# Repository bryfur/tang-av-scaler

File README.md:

# tang-av-scaler

An FPGA video scaler for the sixth generation of game consoles (PlayStation 2, Xbox, GameCube):
480i component video and stereo sound in, 1080p60 HDMI out, about 2 ms behind the console. A Sipeed
Tang Mega 138K SOM (Gowin GW5AST-138) on a carrier board of its own, with a Seeed XIAO ESP32-C5 for
Wi-Fi. The board, the FPGA design, the software for the FPGA's CPU and the ESP32's firmware are all
here.

```
console: component video (YPbPr, 480i) + stereo audio
  -> ADV7181D decoder, PCM1808 audio converter
  -> GW5AST-138 FPGA
       fields into DDR3 -> motion adaptive deinterlace + noise reduction -> SMAA
       -> FSR 1 upscale (EASU) -> FSR 1 sharpen (RCAS) -> on-screen text -> HDMI coding
       its hard RISC-V CPU: bring-up, settings, frame lock, on-screen text
  -> the FPGA's transceivers -> SN65DP159 -> HDMI 1080p60 with sound
  XIAO ESP32-C5: Wi-Fi, web page, updates, JTAG; talks to the CPU over SPI
```

Status (2026-11-12): the board (rev C-B) is built and runs a console's picture and sound to a
display and a capture device. The table below is what it does now, on the board. The console it
has been run with is a PlayStation 2; an Xbox or a GameCube with its component cable puts out the
same signal (480i, YPbPr, 59.94 Hz) and has not been tried yet.

The board, rev C-B ([hardware/av-board/](hardware/av-board/README.md)), as designed (rendered, and from above) and as built:
the SOM under its heat sink, the XIAO and its antenna at the right; along the back edge the HDMI
output, the two audio jacks, power (USB-C) and the three component video jacks.

A frame as it leaves for the display, the on-screen display on (read back from the FPGA: no camera,
no capture device).

Tales of the Abyss, one frozen frame, shown two ways in turn (two seconds each): the console's 480i
stretched the plain way, then the scaler's output; the corner says which.
[Drag a line between them yourself](https://bryfur.github.io/tang-av-scaler/compare/?frame=abyss).

## What it does

| | |
|---|---|
| Input | 480i component (YPbPr) through an ADV7181D, sampled line-locked at 13.5 MHz; stereo analogue audio through a PCM1808. The decoder's sampling phase can be set, or tuned to the console's pixels (every phase tried on a still picture, the sharpest kept). |
| Deinterlacing | Motion adaptive from the last four fields, kept in the SOM's DDR3: a field's lines as they are, the lines between from the field before where nothing moves and from their neighbours where something does. Bob and weave can be chosen instead. |
| Noise | Where the picture is still, each sample is averaged with the same one a frame earlier (off, or three strengths). |
| Anti-aliasing | SMAA 1x on the 480-line picture: luma edges, the orthogonal and the diagonal patterns, corners kept. A view that paints what it finds (edges, blends) in the picture's place, for tuning. |
| Scaling | FSR 1's edge adaptive upsampling (EASU) to 1440 x 1080 (4:3) or 1920 x 1080 (16:9, for a game's widescreen mode). Any part of the source can be shown: the black border round a game's picture is measured and left out, so the picture fills the screen (or the part is set by hand). |
| Sharpening | FSR 1's RCAS on luma, in 16 steps, with its noise term (less where a pixel is noise rather than detail). |
| Timing | The output's frames are kept in step with the input's fields (the CPU trims the clock generator: within 10 us, no field shown twice or left out). A frame is made from the field that is still coming in: about 2 ms from a line captured to it sent (16.8 ms with whole fields). |
| Output | 1080p60 (59.94 Hz) HDMI from the FPGA's own transceivers; the console's sound as HDMI audio (two channels of L-PCM at 48 kHz, its clock from the PLL the pixel clock comes from); AVI and audio InfoFrames. Runs a display, a capture device and an AV receiver (picture and sound). |
| On screen | An on-screen display: what comes in and goes out, what is done to the picture, the delay, the lock, the FPGA's temperature. |
| Control | A web page on the XIAO: every setting (applied as it is changed, kept across power cycles), status, a screen capture of the output read back from the FPGA, firmware update over Wi-Fi. |

## What it looks like

Two frozen frames, each in and out: Killzone (PS2, its widescreen mode) and Tales of the Abyss
(PS2, 4:3). "The plain way" is the
two 480i fields as the console sent them, woven into a frame and stretched to 1080p (bilinear),
which is about what a simple scaler or a display does. "The scaler" is its 1080p output (motion
adaptive deinterlacing, noise reduction medium, SMAA with diagonals and corners at edge threshold
12, FSR 1 with sharpening 8/16). Nothing went through a camera or a capture device: the fields are
read out of the FPGA's memory and the output is read back from its last stage, pixel for pixel
(`gateware/tools/still.py`).

**[Drag to compare](https://bryfur.github.io/tang-av-scaler/compare/)**: both frames on a page with a
line to drag between the plain picture and the scaler's, at any size up to four screen pixels a
pixel (`docs/compare/index.html`).

The pictures themselves, in [`docs/compare/`](docs/compare/):

- Whole frames, 1920 x 1080. Killzone: [the plain way](docs/compare/game-plain.png),
  [the scaler](docs/compare/game-scaler.png), [a half of each](docs/compare/game-split.png).
  Tales of the Abyss: [the plain way](docs/compare/abyss-plain.png),
  [the scaler](docs/compare/abyss-scaler.png), [a half of each](docs/compare/abyss-split.png).
- The frames as they came, the fields woven and nothing else (720 x 480):
  [Killzone](docs/compare/game-480i.png), [Tales of the Abyss](docs/compare/abyss-480i.png).
- Parts of Killzone side by side, three times the size: [the tower and its guy wires](docs/compare/tower.png),
  [palms](docs/compare/palms.png), [hanging foliage](docs/compare/foliage.png),
  [HUD text](docs/compare/hud-text.png), [the ammunition counter](docs/compare/ammo.png).

## How it is put together

- **The picture's path is logic** (`gateware/rtl/`): every pixel, at 148.5 MHz out. Each block has a
  model in Python (`gateware/sim/`) and the whole path is simulated against them pixel for pixel:
  the deinterlacer, SMAA, the scaler and the sharpening give exactly the models' pictures.
- **Everything else runs on the FPGA's hard CPU** (an Andes A25 RISC-V in the GW5AST, `gateware/sw/`,
  no operating system): it brings the board's chips up, holds the settings, finds the picture's
  border, tunes the sampling phase, keeps the output in step with the input, writes the on-screen
  text. A new program is loaded in a second, with no new bitstream.
- **The XIAO ESP32-C5** (`firmware/xiao-wifi/`) is the way in: Wi-Fi, the web page, updates, and
  JTAG to load bitstreams. It talks to the CPU over SPI in small messages, keeps the settings for
  when the power is off, and carries the CPU's program.

The design uses 16 % of the FPGA's logic, 75 % of its block RAM and 15 % of its multipliers.

## Measured on the board

| | |
|---|---|
| Delay | 2.0 ms at the top of the picture (some 2.5 ms at the bottom, by the two scan rates) with the picture made from the field coming in; 16.8 ms with whole fields. From the FPGA's own timing of a frame's start against the field; not yet measured from outside, and a display adds its own. |
| Frame lock | within 10 us of its mark, the clock trimmed by some -57 ppm (this console against this board); in step some 20 s after starting 5 ms off |
| Noise | the spread in a frozen frame's flat areas: 2.32 as it comes, 1.98 with the noise reduction; sharpened fully 3.94, with the sharpening's noise term 3.12, with both 2.61 |
| Sampling phase | 4.5 % between the sharpest and the least sharp phase on Killzone (its picture is soft to begin with) |
| Screen capture | 480 x 270 in 2 s, 960 x 540 in 6 s over the web page |

## What is not done

- Consoles other than the PlayStation 2 have not been tried. The Xbox and the GameCube put out the
  same 480i over their component cables; the Dreamcast has no component output (its VGA and RGB
  would come in at the board's inputs that are not used yet).
- Inputs other than 480i: 480p, 576i, 720p and 1080i need the decoder's settings and the capture's
  timing for each.
- 4K output: a 2160p30 test picture is clean on a display; at 2160p60 the link runs and the display
  sees scrambling but shows nothing; the scaler's own path ends at 1080p.
- The board's other inputs (S/PDIF, VGA, RGB with SCART sync) are wired but not used.
- Without the XIAO the CPU starts with its built-in settings: it has no storage of its own.
- At power-on the FPGA loads its image twice, some 20 s more before there is a picture: configured
  before the clock generator runs, one transceiver lane's clock comes up wrong and the lanes'
  resets do not clear it; the XIAO sees that and has the FPGA load again. The right reset is not
  found yet.
- A bitstream into the FPGA's SRAM over Wi-Fi (`avx.py load`) goes in, and the XIAO then restarts
  with the FPGA left unloaded; over USB it works (`gateware/tools/load.sh`).
- The delay has not been measured through a display with a camera or a light sensor.

## The repository

| Directory | What |
|---|---|
| [`hardware/av-board/`](hardware/av-board/README.md) | The board, rev C-B: generated with KiCad's Python API from `rev-cb/board.py`, every circuit from its part's reference design and reviewed against the data sheets; fab files for JLCPCB. Earlier designs that were not built are in `older/`. |
| [`gateware/`](gateware/README.md) | The FPGA design: `rtl/` the logic, `sw/` the CPU's program, `sim/` the models and testbenches, `gowin/` the build, `tools/` the host's scripts (registers, loading, stills), `docs/` notes. |
| [`firmware/xiao-wifi/`](firmware/xiao-wifi/README.md) | The XIAO ESP32-C5's firmware: Wi-Fi, the web page, updates, a JTAG server, the link to the FPGA's CPU. (`firmware/xiao/` is an earlier USB-only bridge for an ESP32-S3.) |

Building and loading: [gateware/README.md](gateware/README.md) (the bitstream and the CPU's
program: Gowin's tools, a RISC-V GCC) and [firmware/xiao-wifi/README.md](firmware/xiao-wifi/README.md)
(ESP-IDF). With the bitstream in the SOM's flash and the firmware in the XIAO, the board needs
power, a console and a display.

## Reference documents

`hardware/av-board/refs/` (not in git: the vendors' copyright) holds the data sheets and user
guides the circuits follow; [hardware/av-board/README.md](hardware/av-board/README.md) lists which
and where each came from. The scaler's algorithms: SMAA (Jimenez et al.) and AMD's FidelityFX Super
Resolution 1 (EASU and RCAS, MIT licence), both written again for this hardware
(`gateware/sim/smaa.py`, `gateware/sim/fsr.py` say how they differ).

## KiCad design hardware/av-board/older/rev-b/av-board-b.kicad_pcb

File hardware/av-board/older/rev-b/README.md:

# AV board rev B

Rev A with the ADV7842 (256-ball BGA) replaced by the ADV7181D (64-lead LFCSP): component video
into the ADV7181D, stereo audio into a PCM1808, HDMI out of an ADV7511. Four layers, no BGA.

Status: reviewed against every part's data sheet (review.md), routed, DRC clean, fab files made;
not ordered.

- [design.md](design.md): what changed from rev A, and the ADV7181D's circuit with its sources
- [review.md](review.md): every part checked against its data sheet, with the fixes
- `board.py`, `gen_pcb.py`: the sources; made as in [../README.md](../../README.md)

## Ordering at JLCPCB

`fab/av-board-b-gerbers.zip` for the board; for assembly, one of:

| BOM + CPL | Assembled by JLCPCB | By hand |
|---|---|---|
| `fab/av-board-b-bom.csv`, `fab/av-board-b-cpl.csv` | everything (230 parts) | nothing |
| `fab/av-board-b-hand-jacks-bom.csv`, `fab/av-board-b-hand-jacks-cpl.csv` | everything but the RCA jacks (225 parts) | J1-J5: CUI RCJ-014 (yellow) for Y, Pb and L, RCJ-012 (red) for Pr and R, LCSC C4991844 / C4991691, or any RCJ-01x |

Settings the files do not carry:

- 4 layers, 1.6 mm, stack-up **JLC04161H-7628**: F.Cu signal / In1 GND / In2 GND / B.Cu signal
  (the TMDS geometry assumes the 0.21 mm 7628 prepreg under each outer layer). Impedance control
  on: the TMDS pairs are 0.25 mm lines with a 0.25 mm gap on F.Cu, 103 R differential by
  IPC-2141. Confirm in JLCPCB's impedance calculator (outer layer, W 0.25, S 0.25). The voids
  in In1 and In2 under the ESD arrays' TMDS pads are meant (TI SPRAAR7 3.14; review.md's TMDS
  layout row, `kit/hdmi_audit.py rev-b`).
- Vias 0.5/0.3 mm, and four 0.4/0.2 mm ones at the ESD arrays' GND pads (inside JLCPCB's
  0.3/0.15 mm four-layer minimum; check the quote does not add a small-via charge). Minimum track
  and space 0.127 mm.
- Assembly: **top side only**: every SMT part is on the top. Underneath are only the J9/J10
  sockets (through-hole, soldered from the top). Through-hole parts: the two sockets, HDMI's
  shell, and the RCA jacks unless they are left for hand soldering.
- The XIAO itself is not on the BOM: any Seeed XIAO (ESP32-C3, -S3 or -C6) plugs into J11/J12,
  its USB-C towards the HDMI side (silkscreen "XIAO, USB >"). J7 (SCART sync) is a plain 2-pin
  header: SYNC, GND. J13 (S/PDIF) is a 5-pin header: COAX, GND, OPT, GND, 5V (design.md). J8 (VGA) is a 2 x 8 header,
  pin n the DE-15's pin n, for a bracket cable.
- Check every part's rotation in JLCPCB's placement preview, mainly U1 (the ADV7181D: pin 1 at
  the dot, AIN10 at its top left), U2, U3, the regulators and the three resistor arrays RN1-RN3,
  and the RCA jacks' barrels over the edge (the CPL turns the yellow ones 90 degrees for JLCPCB's
  footprint, kit/gen_fab.py JLC_TURN; the red RCJ-012 has no model there and is placed as drawn,
  as the black RCJ-011).

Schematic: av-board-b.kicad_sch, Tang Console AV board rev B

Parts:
C1, C2: 22u; C_0805_2012Metric; LCSC C45783
C3, C5, C6, C7, C8, C25, C26, C27, C32, C33, C35, C38, C41, C43, C46, C47, C48, C49, C50, C52, C54, C56, C58, C60, C63, C65, C67, C73, C74, C75, C76, C77, C81, C82, C83, C84, C85, C86, C87, C88, C89, C90, C91, C92: 100n; C_0402_1005Metric; LCSC C1525
C4, C9, C11, C12, C14, C15, C17, C18, C20: 10u; C_0805_2012Metric; LCSC C15850
C10: 6.8p; C_0402_1005Metric; LCSC C1576
C13, C16, C19, C69, C71: 220p; C_0402_1005Metric; LCSC C1530
C21, C22, C23, C24, C64, C66, C68, C78, C79, C80: 10u; C_0603_1608Metric; LCSC C19702
C28, C29: 1n; C_0402_1005Metric; LCSC C1523
C30, C31: 33p; C_0402_1005Metric; LCSC C1562
C34, C37, C40, C42: 10u; C_0402_1005Metric; LCSC C15525
C36, C39, C45, C51, C53, C55, C57, C59, C61: 10n; C_0402_1005Metric; LCSC C15195
C44: 82n; C_0402_1005Metric; LCSC C277511
C62, C70, C72: 1u; C_0603_1608Metric; LCSC C15849
D1, D3: B5819W; D_SOD-123; LCSC C8598
D2: KT-0603R; LED-SMD_L1.6-W0.8-R-RD; LCSC C2286
D7: 1N4148WS; D_SOD-323; LCSC C2128
D8, D9, D10, D11, D12, D13: TPD1E05U06DPYR; X1SON-2_L1.0-W0.6-P0.65-RD-1; LCSC C436349
F1, F2: 0.2A; F0805; LCSC C883105
FB1, FB2, FB3, FB4: 120R; L_0603_1608Metric; LCSC C14709
J1: RCA Y; CONN-TH_RCJ-011; LCSC C4991844
J2: RCA Pb; CONN-TH_RCJ-011; LCSC C4991844
J3: RCA Pr; CONN-TH_RCJ-011; LCSC C4991691
J4: RCA L; CONN-TH_RCJ-011; LCSC C4991844
J5: RCA R; CONN-TH_RCJ-011; LCSC C4991691
J6: HDMI-001; HDMI-SMD_19P-P0.50-H-F; LCSC C138388
J7: SYNC; HDR-TH_2P-P2.54-V-M; LCSC C492401
J8: VGA; HDR-TH_16P-P2.54-V-M-R2-C8-S2.54; LCSC C68234
J9, J10: 2x20 socket; HDR-TH_40P-P2.54-V-F-R2-C20-S2.54-2; LCSC C5124634
J11: XIAO 5V..D7; HDR-TH_7P-P2.54-V-F; LCSC C22438157
J12: XIAO D0..D6; HDR-TH_7P-P2.54-V-F; LCSC C22438157
J13: SPDIF; HDR-TH_5P-P2.54-V-M; LCSC C492404
L1: 2.2uH; IND-SMD_L3.0-W3.0_FNR30XXS; LCSC C167747
L2, L3, L4: 10uH; IND-SMD_L4.0-W4.0_SMNR4012; LCSC C222882
Q1, Q2: 2N7002; SOT-23-3_L2.9-W1.3-P1.90-LS2.4-BR; LCSC C8545
R1, R2, R7, R8, R9, R10, R11, R12, R41, R45, R46, R53, R54, R55, R57, R59, R77: 10k; R_0402_1005Metric; LCSC C25744
R3, R5, R6: 470; R_0402_1005Metric; LCSC C25117
R4, R14, R63: 100k; R_0402_1005Metric; LCSC C25741
R13: 499k; R_0402_1005Metric; LCSC C25793
R15: 169k; R_0402_1005Metric; LCSC C25758
R16, R18, R20: 30.1k; R_0402_1005Metric; LCSC C29402
R17, R19: 78.7k; R_0402_1005Metric; LCSC C67239
R21, R22, R23, R24, R42, R43, R44, R60: 75; R_0603_1608Metric; LCSC C4275
R25, R61: 1M; R_0402_1005Metric; LCSC C26083
R26: 1.69k; R_0402_1005Metric; LCSC C25870
R27, R28, R29, R30, R31, R32, R33, R34, R47, R48, R62, R64: 33; R_0402_1005Metric; LCSC C25105
R35, R36, R37, R38, R39, R40, R49, R51: 4.7k; R_0402_1005Metric; LCSC C25900
R50, R52: 47k; R_0402_1005Metric; LCSC C25792
R56, R58: 12k; R_0402_1005Metric; LCSC C25752
R65, R66, R67, R68, R69: 49.9; R_0402_1005Metric; LCSC C25120
R70: 887; R_0402_1005Metric; LCSC C55968414
R71, R72, R73, R74, R75, R76: 2k; R_0402_1005Metric; LCSC C4109
R78: 27k; R_0402_1005Metric; LCSC C25771
RN1, RN2, RN3: 33; RES-ARRAY-SMD_0402-8P-L2.0-W1.0-BL; LCSC C25501
SW1, SW2: TS-1187A-B-A-B; SW-SMD_4P-L5.1-W5.1-P3.70-LS6.5-TL_H1.5; LCSC C318884
U1: ADV7181DBCPZ-RL; LFCSP-64_L9.0-W9.0-P0.50-BL-EP7.1; LCSC C514378
U2: ADV7511KSTZ; LQFP-100_L14.0-W14.0-P0.50-LS16.0-BL; LCSC C179459
U3: PCM1808PWR; TSSOP-14_L5.0-W4.4-P0.65-LS6.4-BL; LCSC C55513
U4: TLV62569DBVR; SOT-23-5_L3.0-W1.7-P0.95-LS2.8-BR; LCSC C141836
U5, U6, U7: TPS7A7001DDAR; SOIC-8_L4.9-W3.9-P1.27-LS6.0-BL-EP; LCSC C60719
U8, U9, U10, U19, U20: TPD4E05U06DQAR; USON-10_L2.5-W1.0-P0.50-BL; LCSC C138714
U12: TPS7A2045PDBVR; SOT-23-5_L2.9-W1.6-P0.95-LS2.8-BR; LCSC C2873627
U13: SN74LVC1GU04DBVR; SOT-23-5_L3.0-W1.7-P0.95-LS2.8-BR; LCSC C81934
U14, U15: SN74LVC1G04DBVR; SOT-23-5_L3.0-W1.7-P0.95-LS2.8-BR; LCSC C7827
U21: SN74LVC2G17DBVR; SOT-23-6_L2.9-W1.6-P0.95-LS2.8-BL; LCSC C10429
U22: SN74LVC8T245PWR; TSSOP-24_L7.8-W4.4-P0.65-LS6.4-BL; LCSC C27643
U23: SN74AVC4T245PWR; TSSOP-16_L5.0-W4.4-P0.65-LS6.4-BL; LCSC C81461
Y1: 28.63636MHz 20pF; CRYSTAL-SMD_L5.0-W3.2; LCSC C112564

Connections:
1V8A: C16.1, C17.1, D1.2 (A), FB1.1, FB2.1, R17.1, U6.6 (OUT)
1V8B: C19.1, C20.1, L2.1, L3.1, L4.1, R19.1, U7.6 (OUT)
3V3: C6.1, C8.1, C13.1, C14.1, C15.1, C18.1, C49.1, C67.1, C68.1, C75.1, C76.1, C77.1, C91.1, D1.1 (K), FB3.1, FB4.1, Q1.1 (G), Q2.1 (G), R1.1, R2.1, R10.2, R11.2, R12.2, R15.1, R35.1, R36.1, R49.1, R51.1, R71.1, R72.1, R73.1, R78.1, U2.47 (MVDD), U3.4 (VDD), U5.6 (OUT), U6.2 (EN), U6.3 (IN), U7.2 (EN), U7.3 (IN), U13.5 (VCC), U14.5 (VCC), U15.5 (VCC), U21.5 (VCC), U22.23 (VCCB), U22.24 (VCCB), U23.16 (VCCB)
3V6: C10.1, C11.1, C12.1, L1.2, R13.1, U5.2 (EN), U5.3 (IN)
5VA: C65.1, C66.1, U3.3 (VCC), U12.5 (OUT)
+5V: C1.1, C2.1, C3.1, C9.1, C62.1, D3.2 (A), F1.1, F2.1, J9.11, J10.11, U4.1 (EN), U4.4 (VIN), U12.1 (IN), U12.3 (EN)
AIN_PB: C26.2, U1.47 (AIN8)
AIN_PR: C27.2, U1.45 (AIN6)
AIN_VB: C48.2, U1.48 (AIN9)
AIN_VG: C47.2, U1.35 (AIN2)
AIN_VR: C46.2, U1.46 (AIN7)
AIN_Y: C25.2, U1.49 (AIN10)
ALSB: R39.2, U1.52 (ALSB)
AUD_DIV_L: C69.1, C70.1, R56.2, R57.1
AUD_DIV_R: C71.1, C72.1, R58.2, R59.1
AUD_VINL: C70.2, U3.13 (VINL)
AUD_VINR: C72.2, U3.14 (VINR)
AV_AVDD: C23.1, C60.1, C61.1, FB3.2, U1.41 (AVDD)
AV_C0: R31.1, U1.26 (P2)
AV_C1: R30.1, U1.25 (P3)
AV_C2: RN3.3, U1.19 (P4)
AV_C3: RN3.2, U1.18 (P5)
AV_C4: RN3.1, U1.17 (P6)
AV_C5: R29.1, U1.16 (P7)
AV_C6: R28.1, U1.15 (P8)
AV_C7: R27.1, U1.14 (P9)
AV_DE: R34.1, U1.63 (FIELD/DE)
AV_DVDD: C21.1, C54.1, C55.1, C56.1, C57.1, FB1.2, U1.23 (DVDD), U1.58 (DVDD)
AV_DVDDIO: C24.1, C50.1, C51.1, C52.1, C53.1, FB4.2, R38.1, R39.1, R40.1, U1.4 (DVDDIO), U1.11 (DVDDIO)
AV_HS: R32.1, U1.2 (HS/CS)
AV_LLC: RN3.4, U1.20 (LLC)
AV_PVDD: C22.1, C44.2, C45.2, C58.1, C59.1, FB2.2, U1.31 (PVDD)
AV_VS: R33.1, U1.64 (VS)
AV_Y0: RN2.4, U1.8 (P12)
AV_Y1: RN2.3, U1.7 (P13)
AV_Y2: RN2.2, U1.6 (P14)
AV_Y3: RN2.1, U1.5 (P15)
AV_Y4: RN1.4, U1.62 (P16)
AV_Y5: RN1.3, U1.61 (P17)
AV_Y6: RN1.2, U1.60 (P18)
AV_Y7: RN1.1, U1.59 (P19)
CAPC2: C37.1, C38.1, C39.1, U1.44 (CAPC2)
CAPY1: C34.1, C35.1, C36.1, U1.39 (CAPY1)
CAPY2: C32.1, C33.1, C34.2, C35.2, C36.2, C37.2, C38.2, C39.2, U1.40 (CAPY2)
CEC_PU: D7.2 (A), R78.2
CML: C42.1, C43.1, U1.43 (CML)
ELPF: C45.1, R26.1, U1.30 (ELPF)
ELPF_RC: C44.1, R26.2
ESP_CS: J9.32, R10.1, U22.21 (B1)
ESP_IRQ: J9.33, R11.1, U23.13 (1B1)
ESP_MISO: J9.35, R12.1, U23.12 (1B2)
ESP_MOSI: J9.36, U22.19 (B3)
ESP_SCK: J9.34, U22.20 (B2)
FB_1V8A: C16.2, R17.2, R18.1, U6.7 (FB)
FB_1V8B: C19.2, R19.2, R20.1, U7.7 (FB)
FB_3V3: C13.2, R15.2, R16.1, U5.7 (FB)
FB_3V6: C10.2, R13.2, R14.1, U4.5 (FB)
FMT: R55.1, U3.12 (FMT)
GND: C1.2, C2.2, C3.2, C4.2, C5.2, C6.2, C7.2, C8.2, C9.2, C11.2, C12.2, C14.2, C15.2, C17.2, C18.2, C20.2, C21.2, C22.2, C23.2, C24.2, C30.2, C31.2, C32.2, C33.2, C40.2, C41.2, C42.2, C43.2, C49.2, C50.2, C51.2, C52.2, C53.2, C54.2, C55.2, C56.2, C57.2, C58.2, C59.2, C60.2, C61.2, C62.2, C63.2, C64.2, C65.2, C66.2, C67.2, C68.2, C69.2, C71.2, C73.2, C75.2, C76.2, C77.2, C78.2, C79.2, C80.2, C81.2, C82.2, C83.2, C84.2, C85.2, C86.2, C87.2, C88.2, C89.2, C90.2, C91.2, C92.2, D2.2 (K), D8.2 (GND), D9.2 (GND), D10.2 (GND), D11.2 (GND), D12.2 (GND), D13.2 (GND), J1.1, J2.1, J3.1, J4.1, J5.1, J6.2 (TMDSData2Shield), J6.5 (TMDSData1Shield), J6.8 (TMDSData0Shield), J6.11 (TMDSClockShield), J6.17 (DDC/CECGround), J6.20, J6.21, J6.22, J6.23, J7.2, J8.5, J8.6, J8.7, J8.8, J8.10, J9.12, J10.12, J10.37, J10.38, J10.39, J10.40, J11.2, J13.2, J13.4, R4.2, R9.2, R14.2, R16.2, R18.2, R20.2, R21.2, R22.2, R23.2, R24.2, R37.2, R41.2, R42.2, R43.2, R44.2, R45.2, R46.2, R53.2, R54.2, R55.2, R57.2, R59.2, R60.2, R63.2, R70.2, R74.2, R77.2, SW1.4 (D), SW2.4 (D), U1.3 (GND), U1.10 (GND), U1.24 (GND), U1.57 (GND), U1.65 (EP), U2.3 (DSD0), U2.4 (DSD1), U2.5 (DSD2), U2.6 (DSD3), U2.7 (DSD4), U2.8 (DSD5), U2.9 (DSDCLK), U2.13 (I2S1), U2.14 (I2S2), U2.15 (I2S3), U2.18 (GND), U2.20 (GND), U2.22 (GND), U2.23 (GND), U2.27 (GND), U2.31 (GND), U2.37 (GND), U2.44 (GND), U2.51 (HEAC-), U2.52 (HEAC+), U2.57 (D35), U2.58 (D34), U2.59 (D33), U2.60 (D32), U2.61 (D31), U2.62 (D30), U2.63 (D29), U2.64 (D28), U2.65 (D27), U2.66 (D26), U2.67 (D25), U2.68 (D24), U2.75 (GND), U2.89 (D7), U2.90 (D6), U2.91 (D5), U2.92 (D4), U2.93 (D3), U2.94 (D2), U2.95 (D1), U2.96 (D0), U2.99 (GND), U2.100 (GND), U3.2 (AGND), U3.5 (DGND), U4.2 (GND), U5.1 (NC), U5.4 (NC), U5.5 (NC), U5.8 (GND), U5.9 (EP), U6.1 (NC), U6.4 (NC), U6.5 (NC), U6.8 (GND), U6.9 (EP), U7.1 (NC), U7.4 (NC), U7.5 (NC), U7.8 (GND), U7.9 (EP), U8.3 (GND), U8.8 (GND), U9.3 (GND), U9.8 (GND), U10.3 (GND), U10.8 (GND), U12.2 (GND), U13.3 (GND), U14.3 (GND), U15.3 (GND), U19.3 (GND), U19.8 (GND), U20.3 (GND), U20.8 (GND), U21.2 (GND), U22.6 (A4), U22.7 (A5), U22.8 (A6), U22.9 (A7), U22.10 (A8), U22.11 (GND), U22.12 (GND), U22.13 (GND), U22.22 (~OE), U23.2 (1DIR), U23.3 (2DIR), U23.8 (GND), U23.9 (GND), U23.10 (2B2), U23.11 (2B1), U23.14 (2#OE), U23.15 (1#OE)
HDMI_5V: C92.1, F2.2, J6.18 (+5VPower), R75.1, R76.1
HDMI_CEC: D7.1 (K), J6.13 (CEC), U2.48 (CEC), U8.5 (D2-), U8.6 (NC)
HDMI_HPD: J6.19 (HotPlugDetect), R77.1, U2.30 (HPD), U8.4 (D2+), U8.7 (NC)
HDMI_SCL: J6.15 (SCL), R75.2, U2.53 (DDCSCL), U8.1 (D1+), U8.10 (NC)
HDMI_SDA: J6.16 (SDA), R76.2, U2.54 (DDCSDA), U8.2 (D1-), U8.9 (NC)
IN_BCK: J9.40, U3.8 (BCK)
IN_C0: J10.26, R31.2
IN_C1: J10.25, R30.2
IN_C2: J10.24, RN3.6
IN_C3: J10.23, RN3.7
IN_C4: J10.22, RN3.8
IN_C5: J10.21, R29.2
IN_C6: J10.19, R28.2
IN_C7: J10.18, R27.2
IN_DE: J10.8, R34.2
IN_DOUT: J9.39, U3.9 (DOUT)
IN_HS: J10.13, R32.2
IN_INT: J10.10, R38.2, U1.1 (#INT)
IN_KEY1: J10.31, R1.2, SW1.1 (A)
IN_KEY2: J10.32, R2.2, SW2.1 (A)
IN_LED: J10.33, R3.1
IN_LLC: J10.20, RN3.5
IN_LRCK: J9.38, U3.7 (LRCK)
IN_RESET_N: J10.1, R37.1, U1.51 (#RESET)
IN_SCKI: J9.37, U3.6 (SCKI)
IN_SCL: J10.3, R35.2, U1.54 (SCLK)
IN_SDA: J10.2, R36.2, U1.53 (SDATA)
IN_VS: J10.9, R33.2
IN_Y0: J10.17, RN2.5
IN_Y1: J10.16, RN2.6
IN_Y2: J10.15, RN2.7
IN_Y3: J10.14, RN2.8
IN_Y4: J10.7, RN1.5
IN_Y5: J10.6, RN1.6
IN_Y6: J10.5, RN1.7
IN_Y7: J10.4, RN1.8
LED_A: D2.1 (A), R3.2
MD0: R53.1, U3.10 (MD0)
MD1: R54.1, U3.11 (MD1)
OUT_C0: J9.15, U2.80 (D16)
OUT_C1: J9.13, U2.78 (D17)
OUT_C2: J9.10, U2.74 (D18)
OUT_C3: J9.9, U2.73 (D19)
OUT_C4: J9.8, U2.72 (D20)
OUT_C5: J9.7, U2.71 (D21)
OUT_C6: J9.6, U2.70 (D22)
OUT_C7: J9.5, U2.69 (D23)
OUT_CECCLK: J9.31, U2.50 (CEC_CLK)
OUT_CLK: J9.14, U2.79 (CLK)
OUT_DE: J9.24, U2.97 (DE)
OUT_HSYNC: J9.25, U2.98 (HSYNC)
OUT_I2S0: J9.28, R68.1
OUT_INT: J9.2, R73.2, U2.45 (INT)
OUT_LRCLK: J9.30, R67.1
OUT_MCLK: J9.27, R65.1
OUT_PD: J9.1, R74.1, U2.38 (PD)
OUT_SCL: J9.3, R71.2, U2.55 (SCL)
OUT_SCLK: J9.29, R66.1
OUT_SDA: J9.4, R72.2, U2.56 (SDA)
OUT_SPDIF: J10.28, R69.1
OUT_VSYNC: J9.26, U2.2 (VSYNC)
OUT_Y0: J9.23, U2.88 (D8)
OUT_Y1: J9.22, U2.87 (D9)
OUT_Y2: J9.21, U2.86 (D10)
OUT_Y3: J9.20, U2.85 (D11)
OUT_Y4: J9.19, U2.84 (D12)
OUT_Y5: J9.18, U2.83 (D13)
OUT_Y6: J9.17, U2.82 (D14)
OUT_Y7: J9.16, U2.81 (D15)
PD_FB: R41.1, U1.32 (FB)
PWRDWN: R40.2, U1.29 (#PWRDWN)
RCA_L: J4.2, R56.1
RCA_PB: C26.1, D9.1 (I/O), J2.2, R22.1
RCA_PR: C27.1, D10.1 (I/O), J3.2, R23.1
RCA_R: J5.2, R58.1
RCA_SYNC: C29.1, D11.1 (I/O), J7.1, R24.1
RCA_Y: C25.1, C28.1, D8.1 (I/O), J1.2, R21.1
REFOUT: C40.1, C41.1, U1.42 (REFOUT)
R_EXT: R70.1, U2.28 (R_EXT)
SPDIF_5V: C73.1, F1.2, J13.5
SPDIF_AC: C74.2, R61.2, U13.2 (A)
SPDIF_AMP: R61.1, U13.4 (Y), U14.2 (A)
SPDIF_COAX: C74.1, D12.1 (I/O), J13.1, R60.1
SPDIF_OPT: D13.1 (I/O), J13.3, R63.1, U15.2 (A)
SPDIF_ORX: J10.35, R64.2
SPDIF_OSQ: R64.1, U15.4 (Y)
SPDIF_RX: J10.27, R62.2
SPDIF_SQ: R62.1, U14.4 (Y)
SW_3V6: L1.1, U4.3 (SW)
SYNC_G: C29.2, U1.33 (SOG)
SYNC_Y: C28.2, U1.50 (SOY)
TMDS_CK_N: J6.12 (TMDSClock-), U2.32 (TXC-), U10.5 (D2-), U10.6 (NC)
TMDS_CK_P: J6.10 (TMDSClock+), U2.33 (TXC+), U10.4 (D2+), U10.7 (NC)
TMDS_D0_N: J6.9 (TMDSData0-), U2.35 (TX0-), U10.2 (D1-), U10.9 (NC)
TMDS_D0_P: J6.7 (TMDSData0+), U2.36 (TX0+), U10.1 (D1+), U10.10 (NC)
TMDS_D1_N: J6.6 (TMDSData1-), U2.39 (TX1-), U9.5 (D2-), U9.6 (NC)
TMDS_D1_P: J6.4 (TMDSData1+), U2.40 (TX1+), U9.4 (D2+), U9.7 (NC)
TMDS_D2_N: J6.3 (TMDSData2-), U2.42 (TX2-), U9.2 (D1-), U9.9 (NC)
TMDS_D2_P: J6.1 (TMDSData2+), U2.43 (TX2+), U9.1 (D1+), U9.10 (NC)
TX_AVDD: C79.1, C85.1, C86.1, C87.1, C88.1, L3.2, U2.24 (PVDD), U2.25 (PVDD), U2.29 (AVDD), U2.34 (AVDD), U2.41 (AVDD)
TX_DVDD: C78.1, C81.1, C82.1, C83.1, C84.1, L2.2, U2.1 (DVDD), U2.19 (DVDD), U2.49 (DVDD), U2.76 (DVDD), U2.77 (DVDD)
TX_I2S0: R68.2, U2.12 (I2S0)
TX_LRCLK: R67.2, U2.17 (LRCLK)
TX_MCLK: R65.2, U2.11 (MCLK)
TX_PLVDD: C80.1, C89.1, C90.1, L4.2, U2.21 (PLVDD), U2.26 (BGVDD)
TX_SCLK: R66.2, U2.16 (SCLK)
TX_SPDIF: R69.2, U2.10 (SPDIF)
VGA_5V: J8.9, R50.1, R52.1
VGA_B: C48.1, J8.3, R44.1, U19.5 (D2-), U19.6 (NC)
VGA_G: C47.1, J8.2, R43.1, U19.2 (D1-), U19.9 (NC)
VGA_HS: J8.13, R45.1, U20.1 (D1+), U20.10 (NC), U21.1 (1A)
VGA_HSB: R47.1, U21.6 (1Y)
VGA_HSIN: R47.2, U1.56 (HS_IN/CS_IN)
VGA_R: C46.1, J8.1, R42.1, U19.4 (D2+), U19.7 (NC)
VGA_SCL: J8.15, Q2.3 (D), R52.2, U20.5 (D2-), U20.6 (NC)
VGA_SCL_F: J10.34, Q2.2 (S), R51.2
VGA_SDA: J8.12, Q1.3 (D), R50.2, U20.4 (D2+), U20.7 (NC)
VGA_SDA_F: J10.36, Q1.2 (S), R49.2
VGA_VS: J8.14, R46.1, U20.2 (D1-), U20.9 (NC), U21.3 (2A)
VGA_VSB: R48.1, U21.4 (2Y)
VGA_VSIN: R48.2, U1.55 (VS_IN)
VREF: C63.1, C64.1, U3.1 (VREF)
XIAO_3V3: C5.1, C7.1, J11.3, R4.1, R7.2, R8.2, U22.1 (VCCA), U22.2 (DIR), U23.1 (VCCA)
XIAO_5V: C4.1, D3.1 (K), J11.1
XIAO_D4: J12.5, R7.1, U22.3 (A1)
XIAO_D5: J12.6, R5.2
XIAO_D5_A: R5.1, U23.4 (1A1)
XIAO_D8: J11.6, R8.1, U22.4 (A2)
XIAO_D9: J11.5, R6.2
XIAO_D9_A: R6.1, U23.5 (1A2)
XIAO_D10: J11.4, R9.1, U22.5 (A3)
XTAL: C30.1, R25.1, U1.22 (XTAL), Y1.1 (OSC1)
XTAL1: C31.1, R25.2, U1.21 (XTAL1), Y1.2 (OSC2)

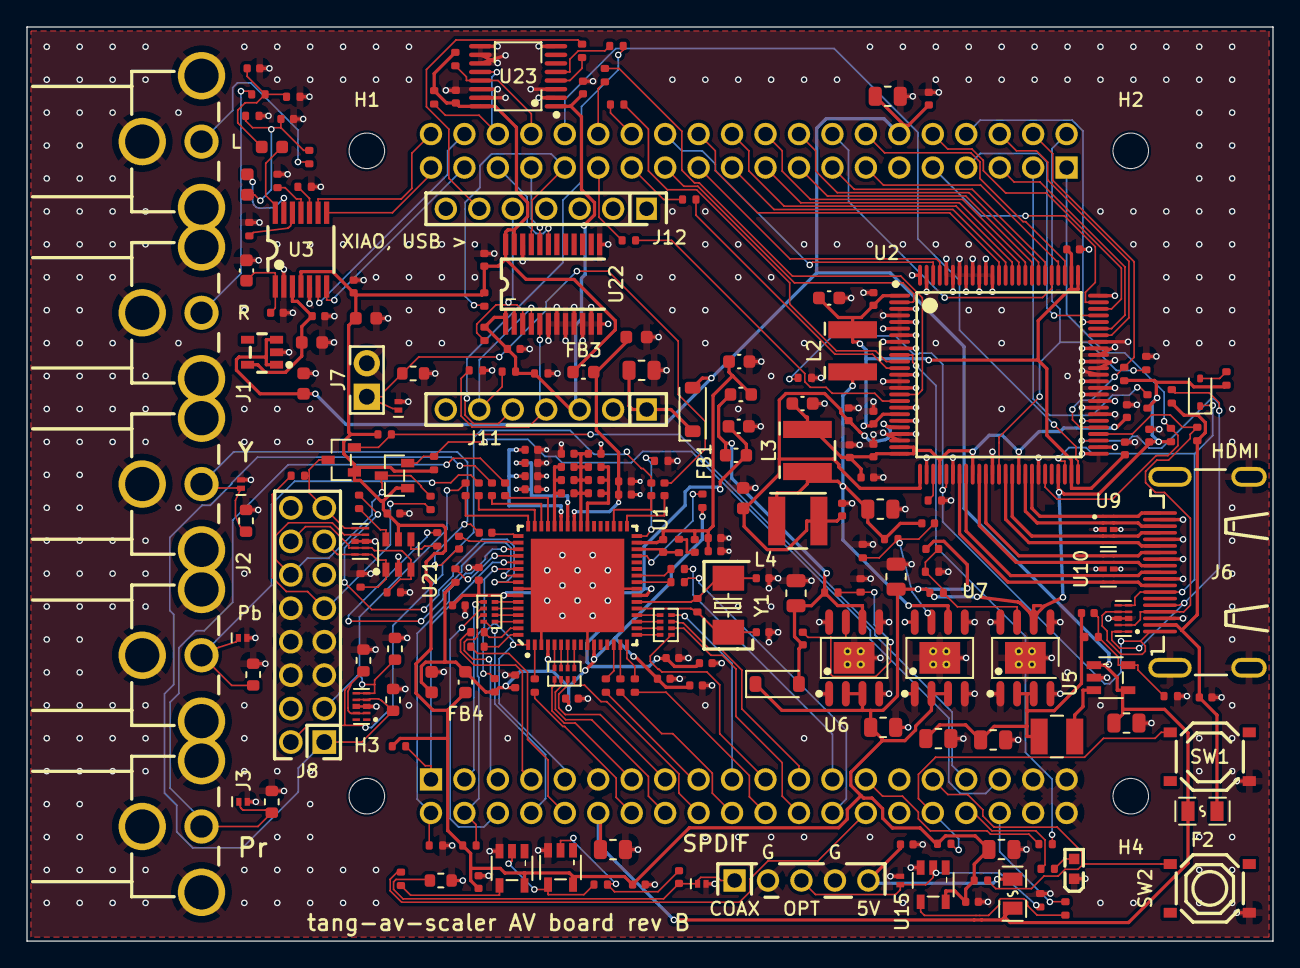
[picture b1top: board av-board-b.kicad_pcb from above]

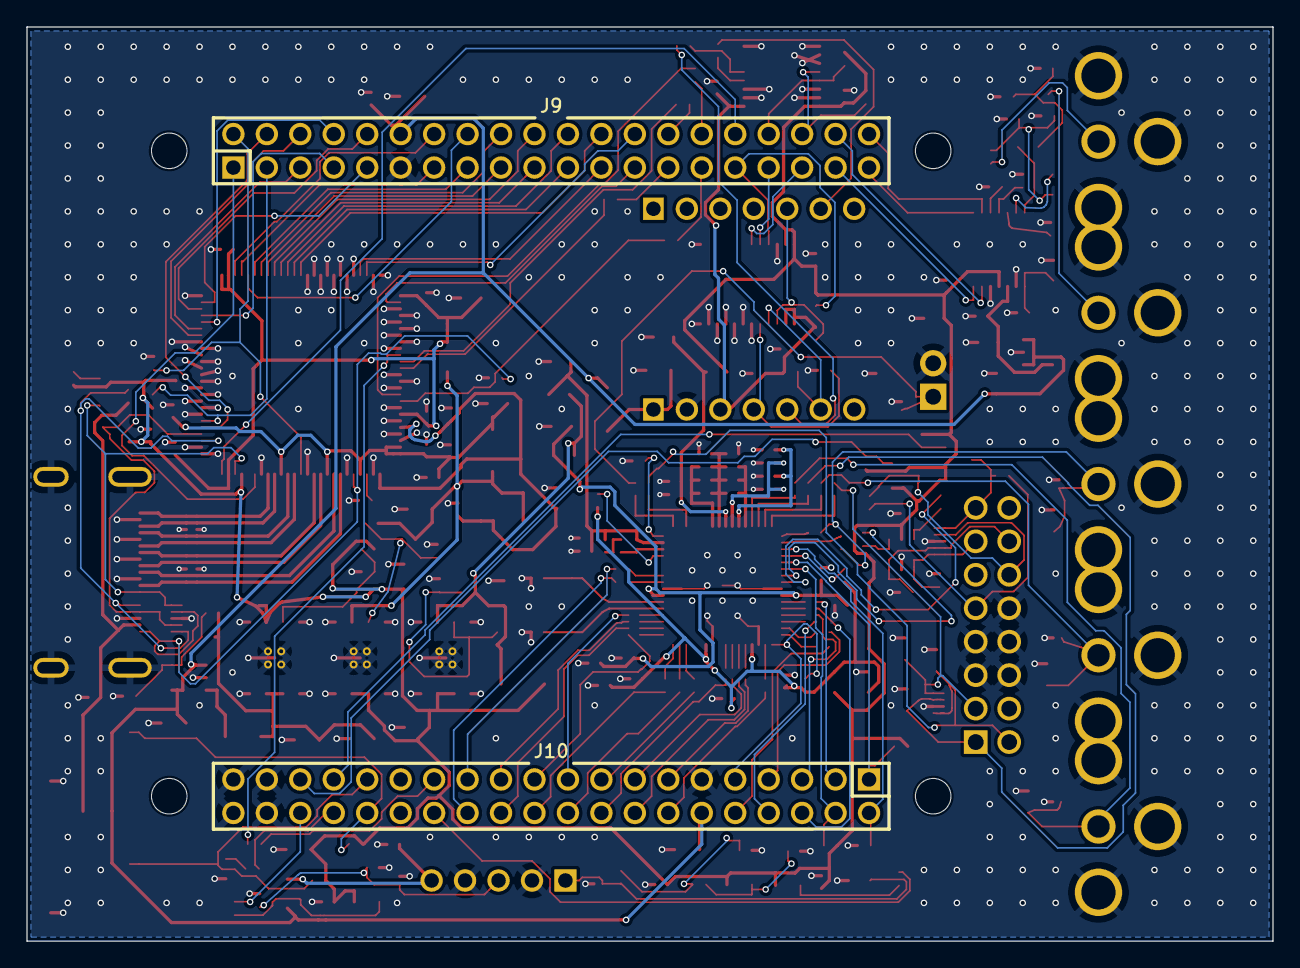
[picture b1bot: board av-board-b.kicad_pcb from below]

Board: 4 copper layers, 94.6 x 69.4 mm, 234 parts (2 on the bottom side), 192 nets.

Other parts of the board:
H1, H2, H3, H4: MountingHole_2.7mm_M2.5

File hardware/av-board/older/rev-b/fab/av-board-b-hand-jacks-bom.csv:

Comment,Designator,Footprint,LCSC Part #
22u,"C1,C2",C_0805_2012Metric,C45783
100n,"C3,C5,C6,C7,C8,C25,C26,C27,C32,C33,C35,C38,C41,C43,C46,C47,C48,C49,C50,C52,C54,C56,C58,C60,C63,C65,C67,C73,C74,C75,C76,C77,C81,C82,C83,C84,C85,C86,C87,C88,C89,C90,C91,C92",C_0402_1005Metric,C1525
10u,"C4,C9,C11,C12,C14,C15,C17,C18,C20",C_0805_2012Metric,C15850
6.8p,C10,C_0402_1005Metric,C1576
220p,"C13,C16,C19,C69,C71",C_0402_1005Metric,C1530
10u,"C21,C22,C23,C24,C64,C66,C68,C78,C79,C80",C_0603_1608Metric,C19702
1n,"C28,C29",C_0402_1005Metric,C1523
33p,"C30,C31",C_0402_1005Metric,C1562
10u,"C34,C37,C40,C42",C_0402_1005Metric,C15525
10n,"C36,C39,C45,C51,C53,C55,C57,C59,C61",C_0402_1005Metric,C15195
82n,C44,C_0402_1005Metric,C277511
1u,"C62,C70,C72",C_0603_1608Metric,C15849
B5819W,"D1,D3",D_SOD-123,C8598
KT-0603R,D2,LED-SMD_L1.6-W0.8-R-RD,C2286
1N4148WS,D7,D_SOD-323,C2128
TPD1E05U06DPYR,"D8,D9,D10,D11,D12,D13",X1SON-2_L1.0-W0.6-P0.65-RD-1,C436349
0.2A,"F1,F2",F0805,C883105
120R,"FB1,FB2,FB3,FB4",L_0603_1608Metric,C14709
HDMI-001,J6,HDMI-SMD_19P-P0.50-H-F,C138388
SYNC,J7,HDR-TH_2P-P2.54-V-M,C492401
VGA,J8,HDR-TH_16P-P2.54-V-M-R2-C8-S2.54,C68234
2x20 socket,"J9,J10",HDR-TH_40P-P2.54-V-F-R2-C20-S2.54-2,C5124634
XIAO 5V..D7,J11,HDR-TH_7P-P2.54-V-F,C22438157
XIAO D0..D6,J12,HDR-TH_7P-P2.54-V-F,C22438157
SPDIF,J13,HDR-TH_5P-P2.54-V-M,C492404
2.2uH,L1,IND-SMD_L3.0-W3.0_FNR30XXS,C167747
10uH,"L2,L3,L4",IND-SMD_L4.0-W4.0_SMNR4012,C222882
2N7002,"Q1,Q2",SOT-23-3_L2.9-W1.3-P1.90-LS2.4-BR,C8545
10k,"R1,R2,R7,R8,R9,R10,R11,R12,R41,R45,R46,R53,R54,R55,R57,R59,R77",R_0402_1005Metric,C25744
470,"R3,R5,R6",R_0402_1005Metric,C25117
100k,"R4,R14,R63",R_0402_1005Metric,C25741
499k,R13,R_0402_1005Metric,C25793
169k,R15,R_0402_1005Metric,C25758
30.1k,"R16,R18,R20",R_0402_1005Metric,C29402
78.7k,"R17,R19",R_0402_1005Metric,C67239
75,"R21,R22,R23,R24,R42,R43,R44,R60",R_0603_1608Metric,C4275
1M,"R25,R61",R_0402_1005Metric,C26083
1.69k,R26,R_0402_1005Metric,C25870
33,"R27,R28,R29,R30,R31,R32,R33,R34,R47,R48,R62,R64",R_0402_1005Metric,C25105
4.7k,"R35,R36,R37,R38,R39,R40,R49,R51",R_0402_1005Metric,C25900
47k,"R50,R52",R_0402_1005Metric,C25792
12k,"R56,R58",R_0402_1005Metric,C25752
49.9,"R65,R66,R67,R68,R69",R_0402_1005Metric,C25120
887,R70,R_0402_1005Metric,C55968414
2k,"R71,R72,R73,R74,R75,R76",R_0402_1005Metric,C4109
27k,R78,R_0402_1005Metric,C25771
33,"RN1,RN2,RN3",RES-ARRAY-SMD_0402-8P-L2.0-W1.0-BL,C25501
TS-1187A-B-A-B,"SW1,SW2",SW-SMD_4P-L5.1-W5.1-P3.70-LS6.5-TL_H1.5,C318884
ADV7181DBCPZ-RL,U1,LFCSP-64_L9.0-W9.0-P0.50-BL-EP7.1,C514378
ADV7511KSTZ,U2,LQFP-100_L14.0-W14.0-P0.50-LS16.0-BL,C179459
PCM1808PWR,U3,TSSOP-14_L5.0-W4.4-P0.65-LS6.4-BL,C55513
TLV62569DBVR,U4,SOT-23-5_L3.0-W1.7-P0.95-LS2.8-BR,C141836
TPS7A7001DDAR,"U5,U6,U7",SOIC-8_L4.9-W3.9-P1.27-LS6.0-BL-EP,C60719
TPD4E05U06DQAR,"U8,U9,U10,U19,U20",USON-10_L2.5-W1.0-P0.50-BL,C138714
TPS7A2045PDBVR,U12,SOT-23-5_L2.9-W1.6-P0.95-LS2.8-BR,C2873627
SN74LVC1GU04DBVR,U13,SOT-23-5_L3.0-W1.7-P0.95-LS2.8-BR,C81934
SN74LVC1G04DBVR,"U14,U15",SOT-23-5_L3.0-W1.7-P0.95-LS2.8-BR,C7827
SN74LVC2G17DBVR,U21,SOT-23-6_L2.9-W1.6-P0.95-LS2.8-BL,C10429
SN74LVC8T245PWR,U22,TSSOP-24_L7.8-W4.4-P0.65-LS6.4-BL,C27643
SN74AVC4T245PWR,U23,TSSOP-16_L5.0-W4.4-P0.65-LS6.4-BL,C81461
28.63636MHz 20pF,Y1,CRYSTAL-SMD_L5.0-W3.2,C112564
